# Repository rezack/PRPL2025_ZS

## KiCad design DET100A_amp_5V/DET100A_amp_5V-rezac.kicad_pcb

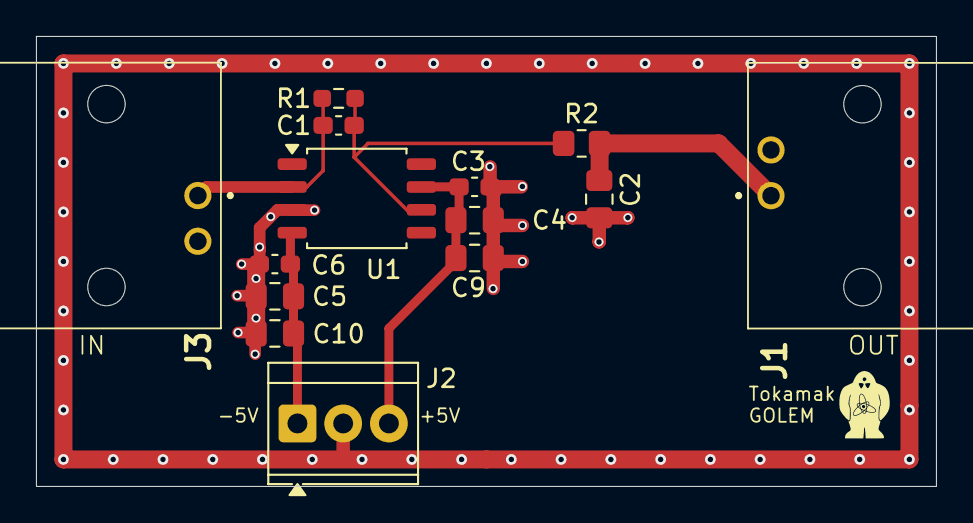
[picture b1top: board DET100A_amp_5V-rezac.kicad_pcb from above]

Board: 2 copper layers, 50.0 x 25.0 mm, 14 parts (0 on the bottom side), 6 nets.

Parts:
C1: 1p; C_0603_1608Metric_Pad1.08x0.95mm_HandSolder
C2: 30n; C_0805_2012Metric_Pad1.18x1.45mm_HandSolder
C3, C6: 1n; C_0603_1608Metric_Pad1.08x0.95mm_HandSolder
C4, C5: 100n; C_0805_2012Metric_Pad1.18x1.45mm_HandSolder
C9, C10: 10u; C_0805_2012Metric_Pad1.18x1.45mm_HandSolder
J1, J3: 5227677-1; 52276771
J2: Screw_Terminal_01x03; TerminalBlock_TE_282834-3_1x03_P2.54mm_Horizontal
R1: 2M; R_0603_1608Metric_Pad0.98x0.95mm_HandSolder
R2: 50; R_0805_2012Metric_Pad1.20x1.40mm_HandSolder
U1: OPA656NB/250; SOIC-8_5.3x5.3mm_P1.27mm

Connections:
GND: C2.1, C3.1, C4.1, C5.1, C6.1, C9.2, C10.1, J1.2 (Ext), J2.2, J3.2 (Ext), U1.3 (NONIINVERTINGINPUT)
unnamed: C2.2, J1.1 (In), R2.2
unnamed: C3.2, C4.2, C9.1, J2.3 (Pin_1), U1.7 (VS+)
unnamed: C5.2, C6.2, C10.2, J2.1 (Pin_3), U1.4 (VS-)
unnamed: C1.1, J3.1 (In), R1.1, U1.2 (INVERTINGINPUT)
unnamed: C1.2, R1.2, R2.1, U1.6 (OUTPUT)

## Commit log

2026-06-11 docs: update GOLEM wiki report
2026-06-12 feat: add some silkscreen elements
2026-06-18 konzultace 18.6.2026, board, 3D print settings
